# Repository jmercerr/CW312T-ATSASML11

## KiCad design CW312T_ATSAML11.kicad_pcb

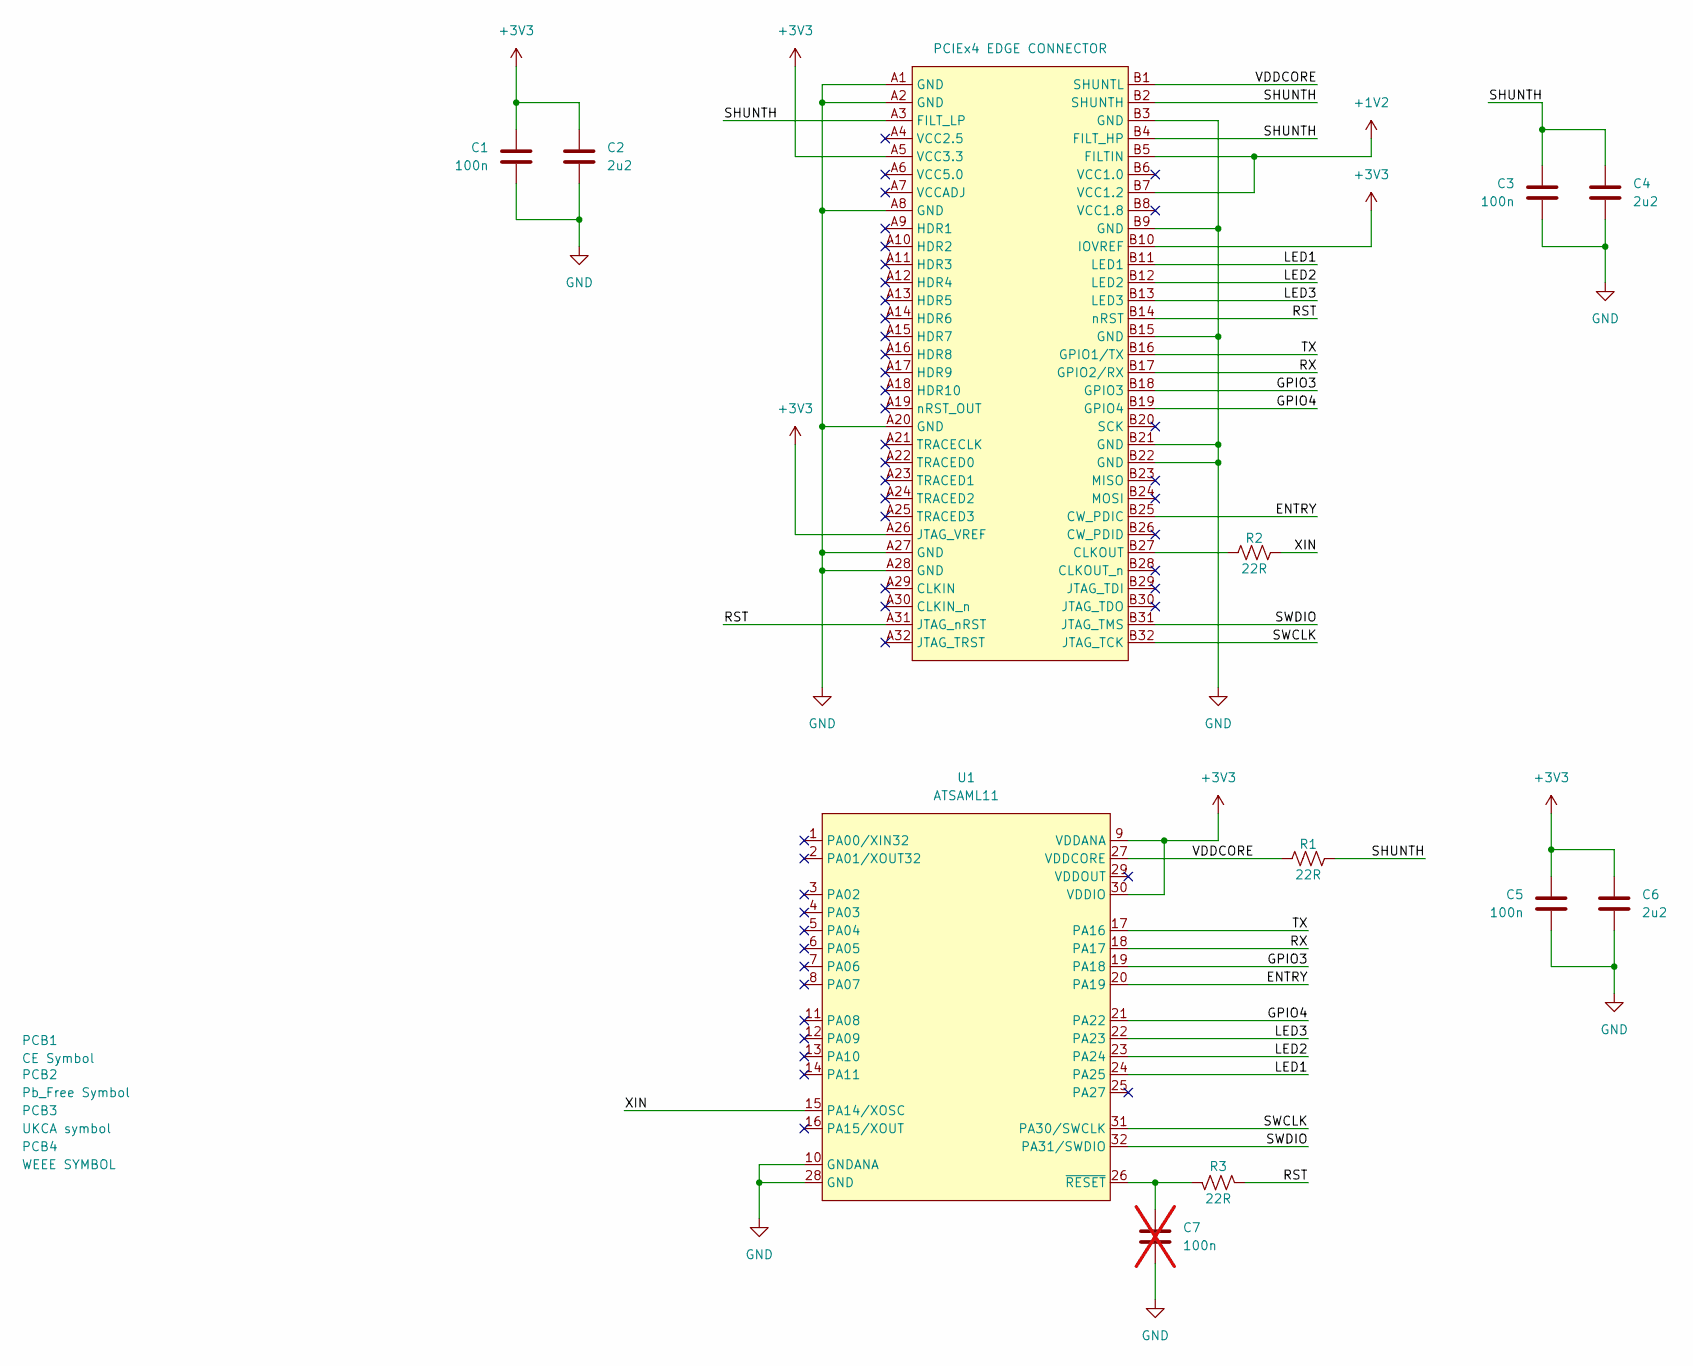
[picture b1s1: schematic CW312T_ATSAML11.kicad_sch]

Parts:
C1, C3, C5: CAP_100n_50V_0603; C_0603_1608Metric; Manufacturer Part Number C0603C104M5RACTU
C2, C4, C6: CAP_2u2_16V_0603; C_0603_1608Metric; Manufacturer Part Number C0603C225K4PAC7867
C7: CAP_100n_50V_0603; C_0603_1608Metric; Manufacturer Part Number C0603C104M5RACTU; not fitted
P1: PCIEx4 EDGE CONNECTOR; CW312_Template
PCB1: CE Symbol; CE-Logo_8.5x6mm_SilkScreen
PCB2: Pb_Free Symbol; Pb_Free_8.0x8.0mm_SilkScreen
PCB3: UKCA symbol; UKCA-Logo_8x8mm_SilkScreen
PCB4: WEEE SYMBOL; WEEE-Logo_5.6x8mm_SilkScreen
R1, R2, R3: 22R_0603; R_0603_1608Metric; Manufacturer Part Number RC0603JR-0722RL
U1: ATSMAL11E16A-AU; TQFP-32_7x7mm_P0.8mm; Manufacturer Part Number ATSAML11E16A-AU

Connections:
+1V2: P1.B5 (FILTIN), P1.B7 (VCC1.2)
+3V3: C1.1, C2.1, C5.1, C6.1, P1.A5 (VCC3.3), P1.A26 (JTAG_VREF), P1.B10 (IOVREF), U1.9 (VDDANA), U1.30 (VDDIO)
/ENTRY: P1.B25 (CW_PDIC), U1.20 (PA19)
/GPIO3: P1.B18 (GPIO3), U1.19 (PA18)
/GPIO4: P1.B19 (GPIO4), U1.21 (PA22)
/LED1: P1.B11 (LED1), U1.24 (PA25)
/LED2: P1.B12 (LED2), U1.23 (PA24)
/LED3: P1.B13 (LED3), U1.22 (PA23)
/RST: P1.A31 (JTAG_nRST), P1.B14 (nRST), R3.2
/RX: P1.B17 (GPIO2/RX), U1.18 (PA17)
/SHUNTH: C3.1, C4.1, P1.A3 (FILT_LP), P1.B2 (SHUNTH), P1.B4 (FILT_HP), R1.2
/SWCLK: P1.B32 (JTAG_TCK), U1.31 (PA30/SWCLK)
/SWDIO: P1.B31 (JTAG_TMS), U1.32 (PA31/SWDIO)
/TX: P1.B16 (GPIO1/TX), U1.17 (PA16)
/VDDCORE: P1.B1 (SHUNTL), R1.1, U1.27 (VDDCORE)
/XIN: R2.2, U1.15 (PA14/XOSC)
GND: C1.2, C2.2, C3.2, C4.2, C5.2, C6.2, C7.2, P1.A1 (GND), P1.A2 (GND), P1.A8 (GND), P1.A20 (GND), P1.A27 (GND), P1.A28 (GND), P1.B3 (GND), P1.B9 (GND), P1.B15 (GND), P1.B21 (GND), P1.B22 (GND), U1.10 (GNDANA), U1.28 (GND)
unnamed: P1.B27 (CLKOUT), R2.1
unnamed: C7.1, R3.1, U1.26 (~RESET)

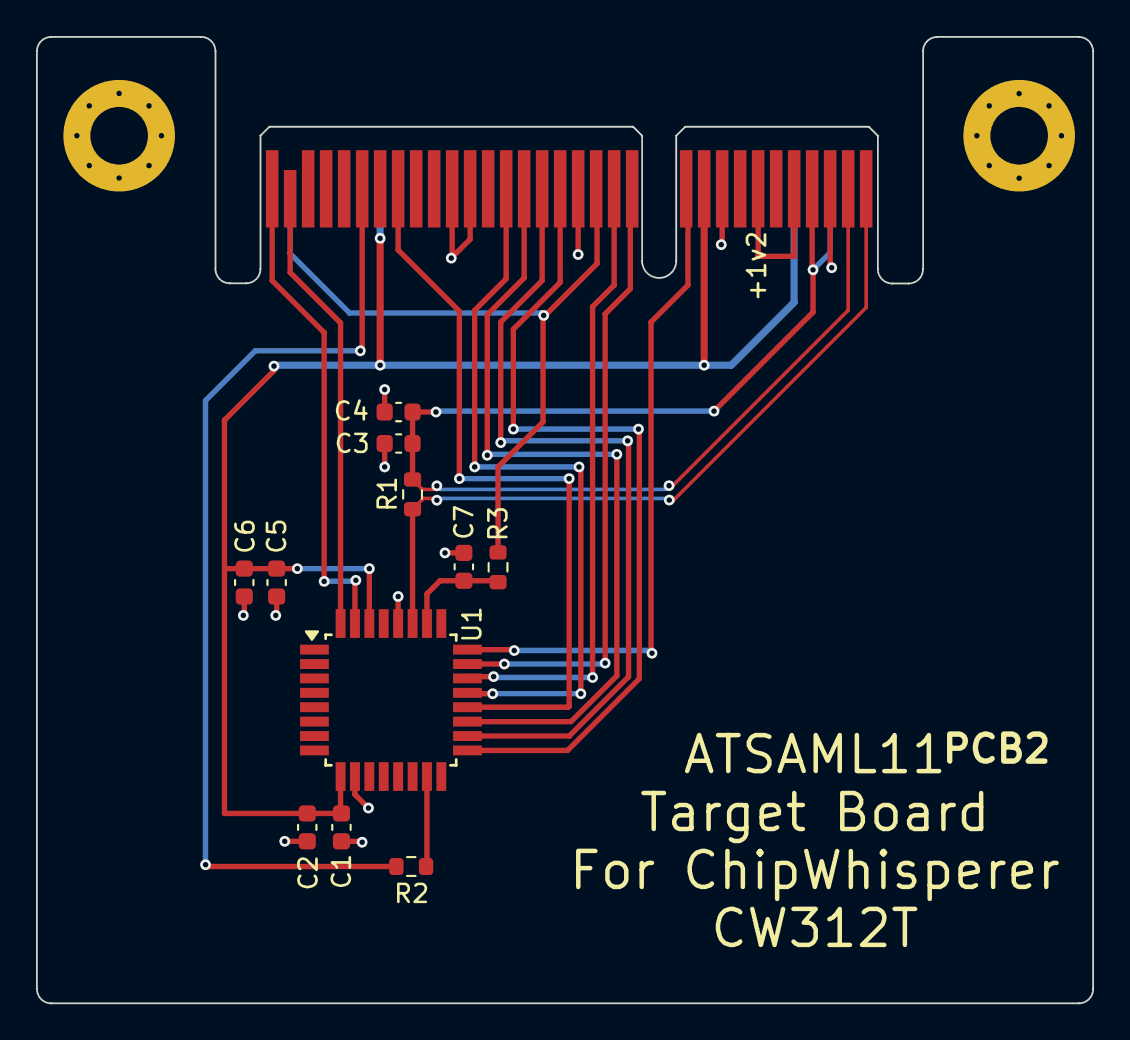
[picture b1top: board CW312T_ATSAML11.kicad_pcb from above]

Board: 2 copper layers, 58.7 x 53.7 mm, 16 parts (0 on the bottom side), 19 nets.

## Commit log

2024-10-21 created repo
2024-10-28 updated pcb based off feedback
2024-11-18 updated ATSAML11 design - Ready for Review
2024-11-21 updated design -removed pin numbers from passives, updated cap placement, updated silkscreen
2024-11-21 Changed how pins were hidden to ensure the nets remain
2024-11-21 updated silkscreen symbols
2024-11-22 updated cw312T template and production files
2024-12-19 updated schematic and pcb after library re-organization
